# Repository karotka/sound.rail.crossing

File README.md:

This is the project of sound railcrossing for DCC railroad. It is based on the ATTINY85 microprocesor. It contains software for ATTINY, circuit and PCB. You can use as DCC Compatible Block Occupancy Detector on isolation rail, switching the railcrossing lights with sound and as servo driver for railway crossing barriers.
It can be use in 2 modes:

1. DCC Compatible Block Occupancy Detector
2. In switch ON/OFF mode

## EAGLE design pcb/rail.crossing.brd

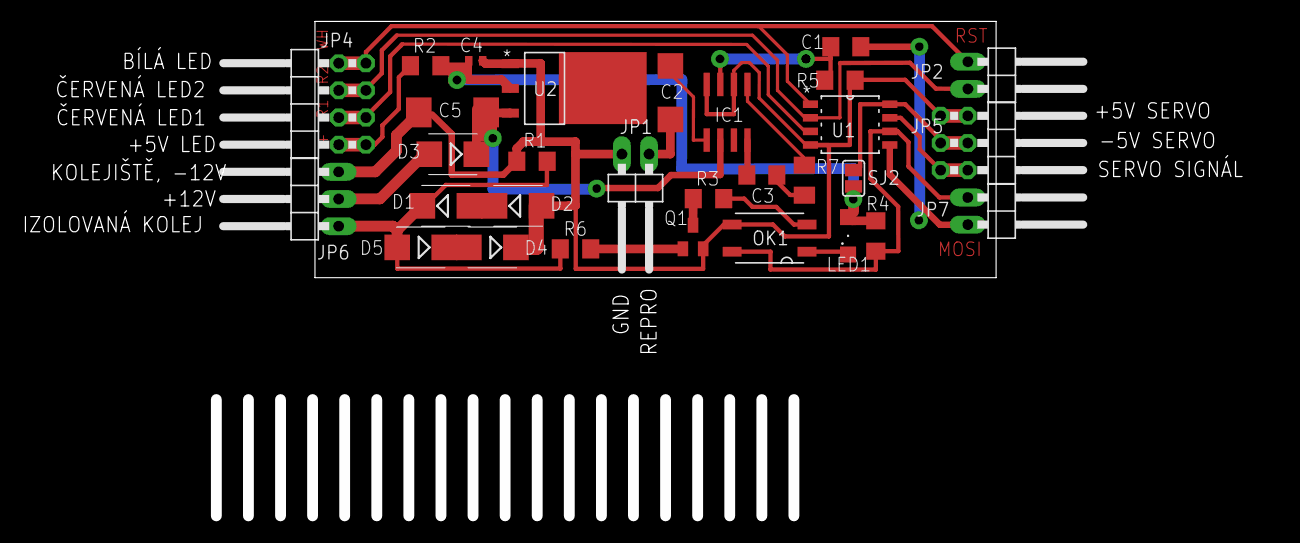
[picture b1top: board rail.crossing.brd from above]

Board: 2 copper layers, 116.5 x 45.7 mm, 30 parts (0 on the bottom side), 25 nets.

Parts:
C1: 100nF; C1206
C2: 100uF; SMC_C
C3: 10uF; C1206
C4: 1uF; C0402
C5: SMC_D
D1, D2, D3, D4, D5: M1; SMB
IC1: LM386M-1; SO08
JP1, JP2, JP7: 1X02/90
JP4: 2X04/90
JP5: 2X03/90
JP6: 1X03/90
LED1: KPT-3216SRD-PRV; SML1206
OK1: PC357N14; SMD4
Q1: BC847SMD; SOT23
R1: 2k2; R1206
R2, R3: 220; R1206
R4, R5: 10K; R1206
R6: 1K; R1206
R7: 1K; M1206
SJ2: SJ
U1: ATTINY85V-10SU; SOIC127P798X216-8N
U2: LM1117MP-5.0; SOT230P696X180-4N

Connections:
220: LED1.C, OK1.1
JP1: D3.C, D5.A, JP6.1, R1.1, R6.1
JP2: C4.2, D2.A, D4.C, IC1.2, IC1.4, JP1.2, JP5.1, JP5.2, JP6.3, OK1.3, Q1.2, R1.2, R5.2, U1.4, U2.1
unnamed: C2.-, JP1.1
unnamed: C3.1, R7.1
unnamed: C3.2, IC1.8
unnamed: D2.C, D3.A
unnamed: D4.A, D5.C
unnamed: Q1.1, R6.2
unnamed: Q1.3, R3.1
unnamed: C2.+, IC1.5
unnamed: OK1.2, R3.2
unnamed: JP5.5, JP5.6, U1.7
unnamed: C1.1, JP7.2, U1.5
unnamed: JP4.1, JP4.2, R2.1
unnamed: JP7.1, OK1.4, R4.1, U1.6
unnamed: JP5.3, JP5.4, LED1.A, R2.2, R4.2, SJ2.2, U1.8
unnamed: IC1.1, R7.2
unnamed: C1.2, IC1.3, R5.1
unnamed: C4.1, SJ2.1, U2.2
unnamed: D1.A, JP6.2
unnamed: C5.+, D1.C, IC1.6, U2.3
RED1: JP2.2, JP4.5, JP4.6, U1.2
RED2: JP4.3, JP4.4, U1.3
WHITE: JP2.1, JP4.7, JP4.8, U1.1

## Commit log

2013-01-09 Add src
2013-01-09 Add res and pcb
2013-01-09 First readme
2013-01-09 Simple readme
2013-01-11 Adding pcg schema
2013-01-13 Add board
2013-01-18 add pcb board and circuit
2013-01-18 mv schema to circuit
2013-01-18 set pwm to zero after stop
2013-01-26 adding new file
2013-01-26 add new board witch mask
2013-04-05 Disable pwm
